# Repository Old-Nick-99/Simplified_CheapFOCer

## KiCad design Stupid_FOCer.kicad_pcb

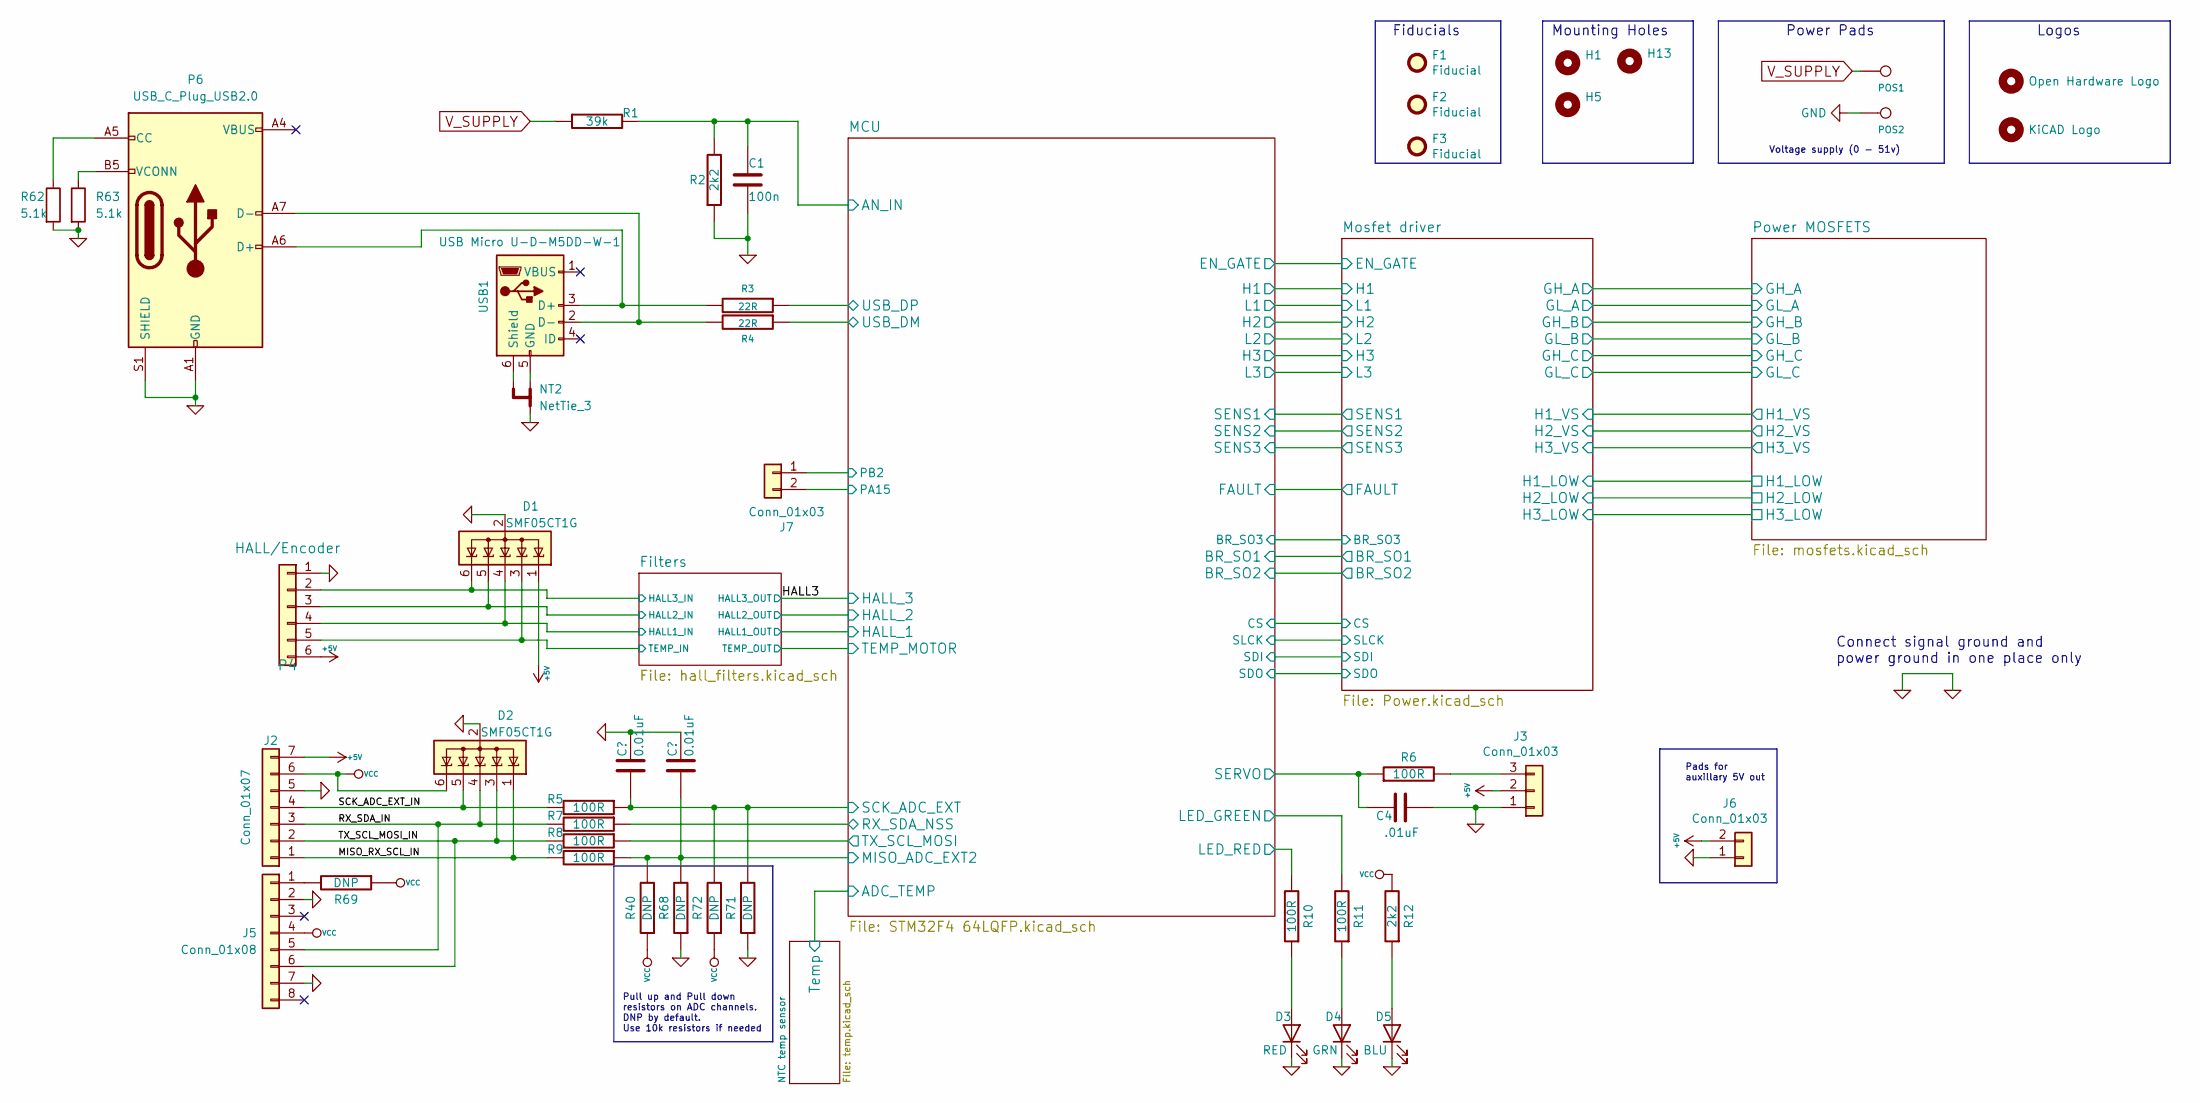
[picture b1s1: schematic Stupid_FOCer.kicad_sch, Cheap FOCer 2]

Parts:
C1: 100n; C_0603_1608Metric
C2, C3: 0.01uF; C_0603_1608Metric
C4: .01uF; C_0603_1608Metric
D1, D2: SMF05CT1G; SOT-363_SC-70-6
D3: RED; LED_0603_1608Metric
D4: GRN; LED_0603_1608Metric
D5: BLU; LED_0603_1608Metric
F1, F2, F3: Fiducial; Fiducial_1mm_Dia_2mm_Outer
H1, H5, H13: MountingHole; MountingHole_3.2mm_M3_ISO14580
H4: Open Hardware Logo; OSHW-Logo2_9.8x8mm_SilkScreen
H9: KiCAD Logo; KiCad-Logo2_5mm_SilkScreen
J2: Conn_01x07; JST_PH_B7B-PH-K_1x07_P2.00mm_Vertical
J3: Conn_01x03; JST_PH_B3B-PH-K_1x03_P2.00mm_Vertical
J5: Conn_01x08; PinSocket_1x08_P2.54mm_Vertical
J6, J7: Conn_01x03; PinHeader_1x02_P2.54mm_Vertical
NT2: NetTie_3; NetTie-3_SMD_Pad0.5mm
P4: HALL/Encoder; JST_PH_B6B-PH-K_1x06_P2.00mm_Vertical
P6: USB_C_Plug_USB2.0; USB_C_Receptacle_JAE_DX07S016JA1R1500
POS1, POS2: POS; MountingPad
R1: 39k; R_0603_1608Metric
R2, R12: 2k2; R_0603_1608Metric
R3, R4: 22R; R_0603_1608Metric
R5, R6, R7, R8, R9, R10, R11: 100R; R_0603_1608Metric
R40, R68, R69, R71, R72: DNP; R_0603_1608Metric
R62, R63: 5.1k; R_0603_1608Metric
USB1: USB Micro U-D-M5DD-W-1; USB_Micro-B_Wuerth_614105150721_Vertical

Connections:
+5V: D1.1 (K), J2.7, J3.2, J6.2, P4.6; also elsewhere on the board
/Filters/HALL1_IN: D1.4 (K), P4.4; also elsewhere on the board
/Filters/HALL2_IN: D1.5 (K), P4.3; also elsewhere on the board
/Filters/TEMP_IN: D1.3 (K), P4.5; also elsewhere on the board
/HALL3: D1.6 (K), P4.2; also elsewhere on the board
/MCU/AN_IN: C1.2, R1.2, R2.2; also elsewhere on the board
/MCU/LED_GREEN: R11.2; also elsewhere on the board
/MCU/LED_RED: R10.2; also elsewhere on the board
/MCU/MISO_ADC_EXT2: C3.2, R9.1, R40.2, R68.2; also elsewhere on the board
/MCU/RX_SDA_NSS: R7.1; also elsewhere on the board
/MCU/SCK_ADC_EXT: C2.2, R5.1, R71.2, R72.2; also elsewhere on the board
/MCU/SERVO: C4.2, R6.1; also elsewhere on the board
/MCU/TX_SCL_MOSI: R8.1; also elsewhere on the board
/MCU/USB_DM: R4.1; also elsewhere on the board
/MCU/USB_DP: R3.1; also elsewhere on the board
/MISO_RX_SCL_IN: D2.1 (K), J2.1, R9.2
/RX_SDA_IN: D2.4 (K), J2.3, J5.5, R7.2
/SCK_ADC_EXT_IN: D2.5 (K), J2.4, R5.2
/TX_SCL_MOSI_IN: D2.3 (K), J2.2, J5.6, R8.2
unnamed: D3.2 (A), R10.1
unnamed: D4.2 (A), R11.1
unnamed: D5.2 (A), R12.1
unnamed: J3.3, R6.2
unnamed: J5.1, R69.2
unnamed: P6.A5 (CC), R62.1
unnamed: P6.A6 (D+), R3.2, USB1.3 (D+)
unnamed: P6.A7 (D-), R4.2, USB1.2 (D-)
unnamed: P6.B5 (VCONN), R63.1
unnamed: NT2.1, USB1.5 (GND)
unnamed: NT2.3, USB1.6 (Shield)
PA15: J7.2; also elsewhere on the board
PB2: J7.1; also elsewhere on the board
VCC: D2.6 (K), J2.6, J5.4, R12.2, R40.1, R69.1, R72.1; also elsewhere on the board
V_SUPPLY: POS1.1, R1.1; also elsewhere on the board

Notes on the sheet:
Power Pads
Fiducials
Logos
Mounting Holes
Connect signal ground and power ground in one place only
Voltage supply (0 - 51v)
Pads for auxillary 5V out
Pull up and Pull down resistors on ADC channels. DNP by default. Use 10k resistors if needed

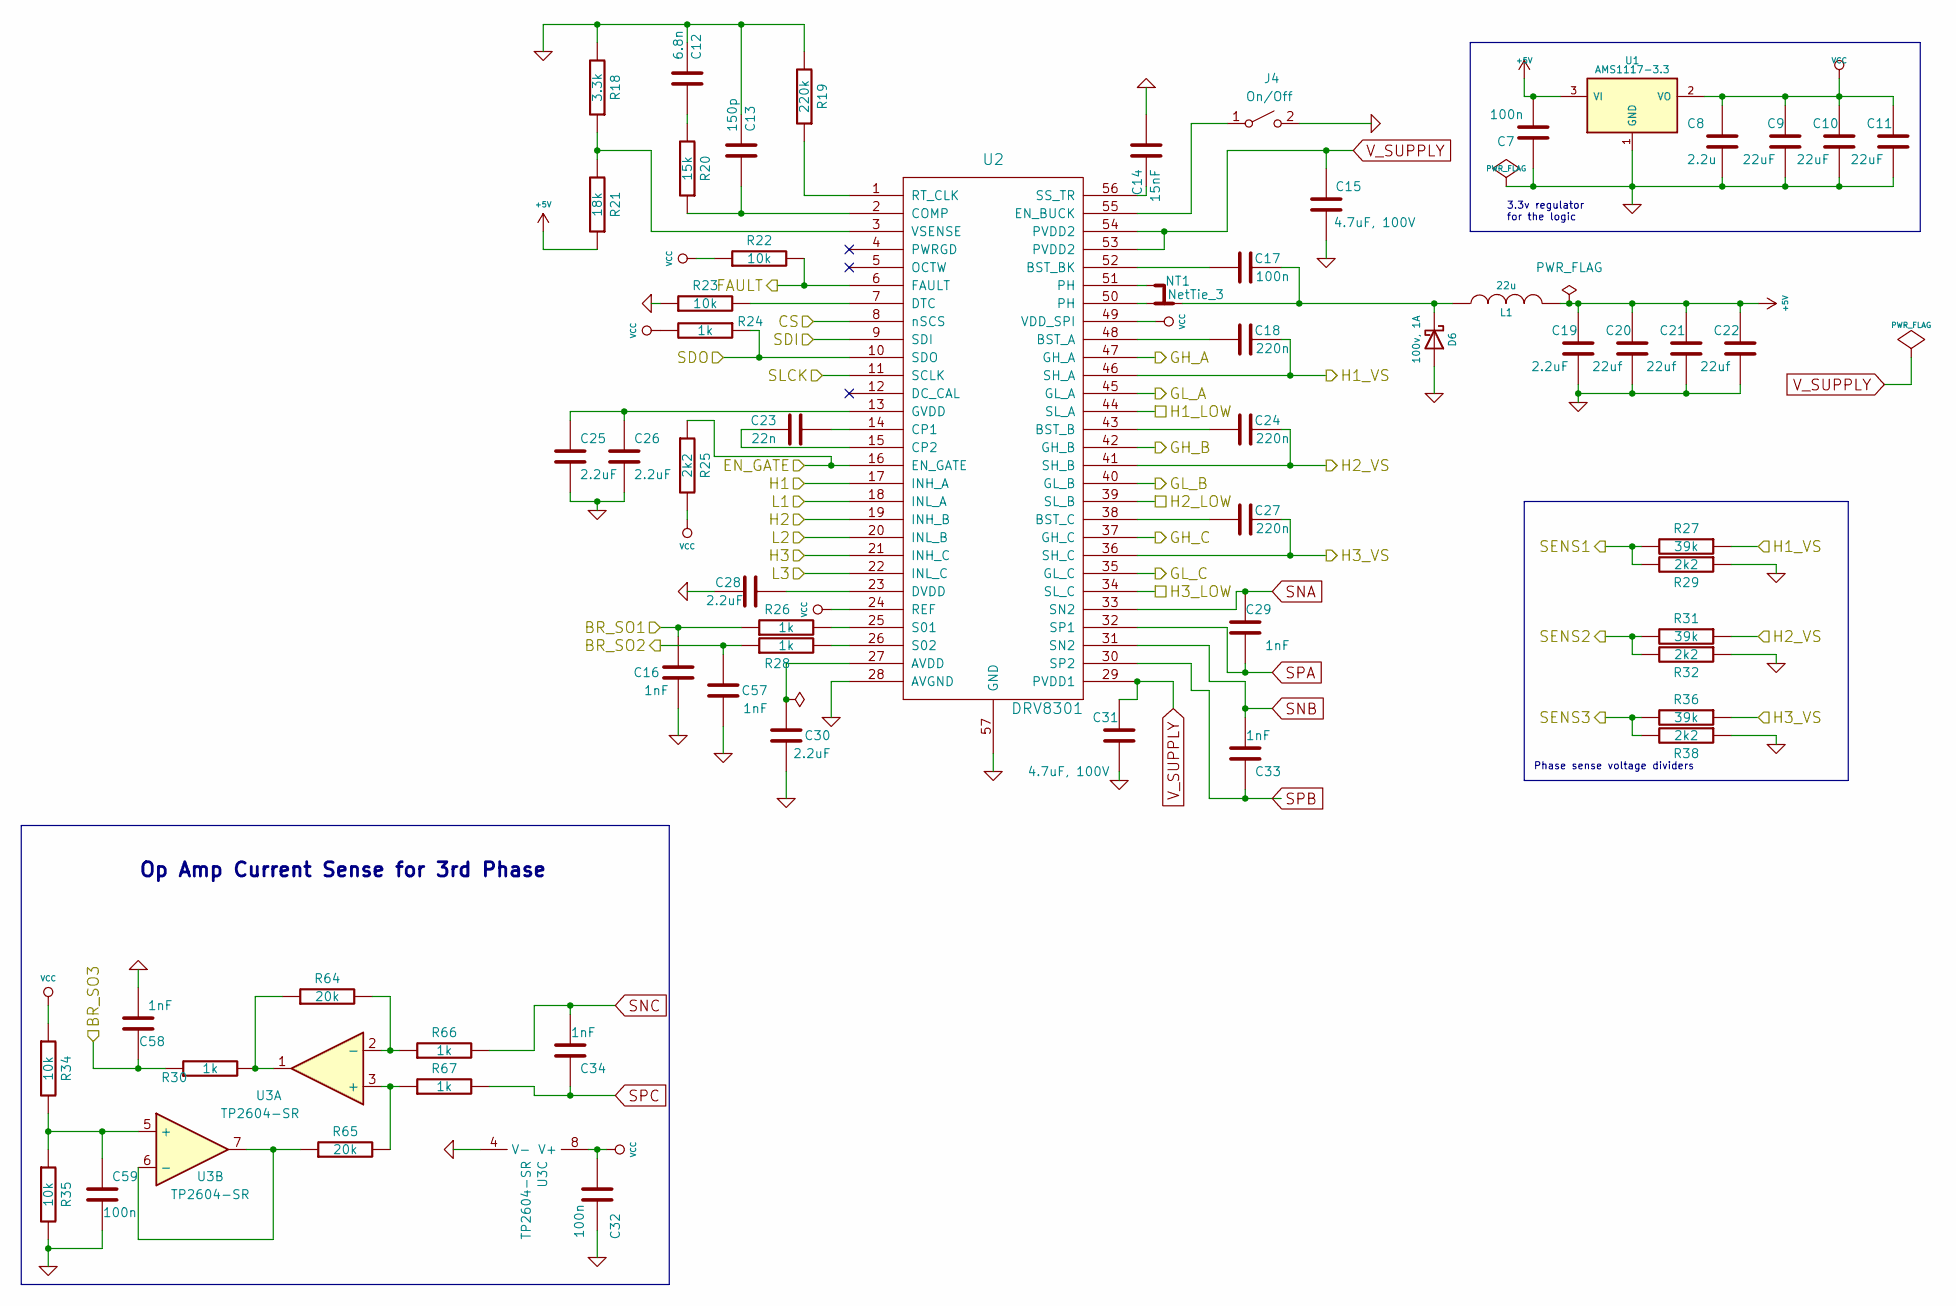
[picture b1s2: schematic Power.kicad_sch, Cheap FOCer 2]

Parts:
C7, C17, C32, C59: 100n; C_0603_1608Metric
C8: 2.2u; C_0603_1608Metric
C9, C10, C11: 22uF; C_0805_2012Metric
C12: 6.8n; C_0603_1608Metric
C13: 150p; C_0603_1608Metric
C14: 15nF; C_0603_1608Metric
C15, C31: 4.7uF, 100V; C_1210_3225Metric
C16, C29, C33, C34, C57, C58: 1nF; C_0603_1608Metric
C18, C24, C27: 220n; C_0603_1608Metric
C19, C25, C26, C28, C30: 2.2uF; C_0603_1608Metric
C20, C21, C22: 22uf; C_0805_2012Metric
C23: 22n; C_0603_1608Metric
D6: 100v, 1A; D_SMA
J4: On/Off; JST_PH_B2B-PH-K_1x02_P2.00mm_Vertical
L1: 22u; L_Taiyo-Yuden_NR-60xx_HandSoldering
NT1: NetTie_3; NT3_Small
R18: 3.3k; R_0603_1608Metric
R19: 220k; R_0603_1608Metric
R20: 15k; R_0603_1608Metric
R21: 18k; R_0603_1608Metric
R22, R23, R34, R35: 10k; R_0603_1608Metric
R24, R26, R28, R30, R66, R67: 1k; R_0603_1608Metric
R25, R29, R32, R38: 2k2; R_0603_1608Metric
R27, R31, R36: 39k; R_0603_1608Metric
R64, R65: 20k; R_0603_1608Metric
U1: AMS1117-3.3; SOT-223-3_TabPin2
U2: DRV8301; HTSSOP-56-1EP_6.1x14mm_P0.5mm_EP3.61x6.35mm
U3: TP2604-SR; SOIC-8_3.9x4.9mm_P1.27mm

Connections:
+5V: C7.2, C19.2, C20.2, C21.2, C22.2, L1.2, R21.1, U1.3 (VI); also elsewhere on the board
/MCU/BR_SO1: C16.2, R26.1; also elsewhere on the board
/MCU/BR_SO2: C57.2, R28.1; also elsewhere on the board
/MCU/BR_SO3: C58.2, R30.1; also elsewhere on the board
/MCU/CS: U2.8 (nSCS); also elsewhere on the board
/MCU/EN_GATE: R25.1, U2.16 (EN_GATE); also elsewhere on the board
/MCU/FAULT: R22.2, U2.6 (FAULT); also elsewhere on the board
/MCU/H1: U2.17 (INH_A); also elsewhere on the board
/MCU/H2: U2.19 (INH_B); also elsewhere on the board
/MCU/H3: U2.21 (INH_C); also elsewhere on the board
/MCU/L1: U2.18 (INL_A); also elsewhere on the board
/MCU/L2: U2.20 (INL_B); also elsewhere on the board
/MCU/L3: U2.22 (INL_C); also elsewhere on the board
/MCU/SDI: U2.9 (SDI); also elsewhere on the board
/MCU/SDO: R24.1, U2.10 (SDO); also elsewhere on the board
/MCU/SENS1: R27.2, R29.2; also elsewhere on the board
/MCU/SENS2: R31.2, R32.2; also elsewhere on the board
/MCU/SENS3: R36.2, R38.2; also elsewhere on the board
/MCU/SLCK: U2.11 (SCLK); also elsewhere on the board
/Mosfet driver/GH_A: U2.47 (GH_A); also elsewhere on the board
/Mosfet driver/GH_B: U2.42 (GH_B); also elsewhere on the board
/Mosfet driver/GH_C: U2.37 (GH_C); also elsewhere on the board
/Mosfet driver/GL_A: U2.45 (GL_A); also elsewhere on the board
/Mosfet driver/GL_B: U2.40 (GL_B); also elsewhere on the board
/Mosfet driver/GL_C: U2.35 (GL_C); also elsewhere on the board
/Mosfet driver/H1_LOW: U2.44 (SL_A); also elsewhere on the board
/Mosfet driver/H1_VS: C18.2, R27.1, U2.46 (SH_A); also elsewhere on the board
/Mosfet driver/H2_LOW: U2.39 (SL_B); also elsewhere on the board
/Mosfet driver/H2_VS: C24.2, R31.1, U2.41 (SH_B); also elsewhere on the board
/Mosfet driver/H3_LOW: U2.34 (SL_C); also elsewhere on the board
/Mosfet driver/H3_VS: C27.2, R36.1, U2.36 (SH_C); also elsewhere on the board
unnamed: C12.2, R20.2
unnamed: C17.2, D6.1 (K), L1.1, NT1.2
unnamed: J4.1 (A), U2.55 (EN_BUCK)
unnamed: NT1.1, U2.50 (PH)
unnamed: NT1.3, U2.51 (PH)
unnamed: R30.2, R64.1, U3.1
unnamed: C30.2, U2.27 (AVDD)
unnamed: C18.1, U2.48 (BST_A)
unnamed: C24.1, U2.43 (BST_B)
unnamed: C17.1, U2.52 (BST_BK)
unnamed: C27.1, U2.38 (BST_C)
unnamed: C13.2, R20.1, U2.2 (COMP)
unnamed: C23.2, U2.14 (CP1)
unnamed: C23.1, U2.15 (CP2)
unnamed: R23.2, U2.7 (DTC)
unnamed: C28.1, U2.23 (DVDD)
unnamed: C25.1, C26.1, U2.13 (GVDD)
unnamed: R19.1, U2.1 (RT_CLK)
unnamed: R26.2, U2.25 (S01)
unnamed: R28.2, U2.26 (S02)
unnamed: C14.1, U2.56 (SS_TR)
unnamed: R18.1, R21.2, U2.3 (VSENSE)
unnamed: R65.2, R67.1, U3.3 (+)
unnamed: R64.2, R66.1, U3.2 (-)
unnamed: C59.1, R34.2, R35.1, U3.5 (+)
unnamed: R65.1, U3.6 (-), U3.7
SNA: C29.2, U2.33 (SN2); also elsewhere on the board
SNB: C33.1, U2.31 (SN2); also elsewhere on the board
SNC: C34.1, R66.2; also elsewhere on the board
SPA: C29.1, U2.32 (SP1); also elsewhere on the board
SPB: C33.2, U2.30 (SP2); also elsewhere on the board
SPC: C34.2, R67.2; also elsewhere on the board
VCC: C8.1, C9.2, C10.2, C11.2, C32.2, R22.1, R24.2, R25.2, R34.1, U1.2 (VO), U2.24 (REF), U2.49 (VDD_SPI), U3.8 (V+); also elsewhere on the board
V_SUPPLY: C15.2, C31.2, U2.29 (PVDD1), U2.53 (PVDD2), U2.54 (PVDD2); also elsewhere on the board

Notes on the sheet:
Phase sense voltage dividers
3.3v regulator for the logic
Op Amp Current Sense for 3rd Phase

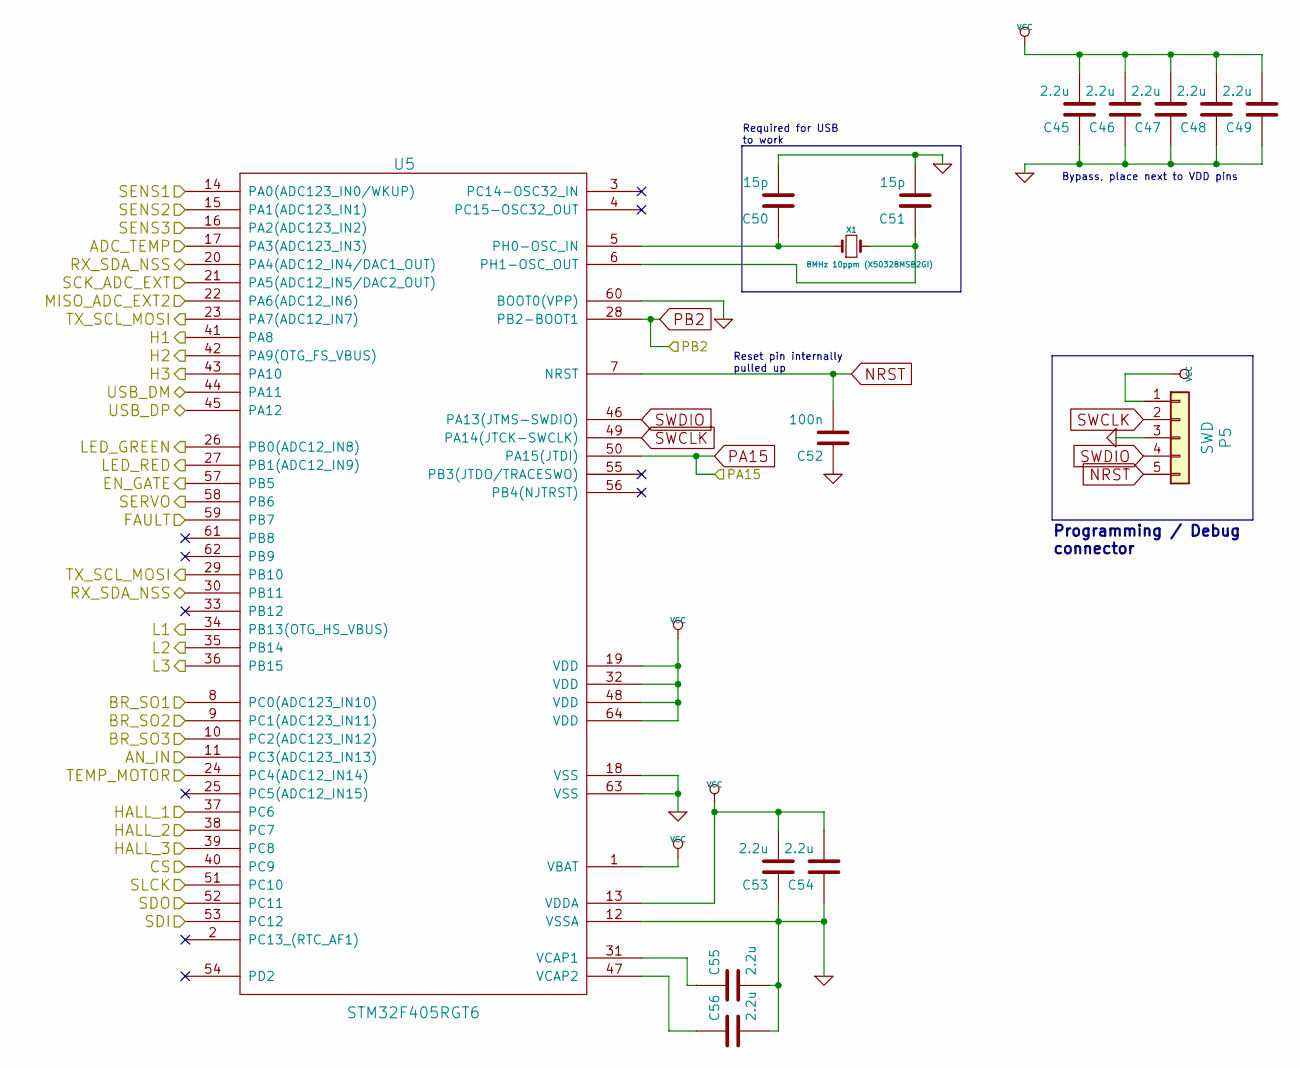
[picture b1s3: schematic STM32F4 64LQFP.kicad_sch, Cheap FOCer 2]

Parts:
C45, C46, C47, C48, C49, C53, C54, C55, C56: 2.2u; C_0603_1608Metric
C50, C51: 15p; C_0603_1608Metric
C52: 100n; C_0603_1608Metric
P5: SWD; PinHeader_1x05_P2.54mm_Vertical
U5: STM32F405RGT6; LQFP-64_10x10mm_P0.5mm
X1: 8MHz 10ppm (X50328MSB2GI); Crystal_SMD_5032-2Pin_5.0x3.2mm; mfg# ABM3B-8.0-10-1UT

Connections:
/Filters/HALL1_IN: U5.37 (PC6); also elsewhere on the board
/Filters/HALL2_IN: U5.38 (PC7); also elsewhere on the board
/Filters/TEMP_IN: U5.24 (PC4(ADC12_IN14)); also elsewhere on the board
/HALL3: U5.39 (PC8); also elsewhere on the board
/MCU/ADC_TEMP: U5.17 (PA3(ADC123_IN3)); also elsewhere on the board
/MCU/AN_IN: U5.11 (PC3(ADC123_IN13)); also elsewhere on the board
/MCU/BR_SO1: U5.8 (PC0(ADC123_IN10)); also elsewhere on the board
/MCU/BR_SO2: U5.9 (PC1(ADC123_IN11)); also elsewhere on the board
/MCU/BR_SO3: U5.10 (PC2(ADC123_IN12)); also elsewhere on the board
/MCU/CS: U5.40 (PC9); also elsewhere on the board
/MCU/EN_GATE: U5.57 (PB5); also elsewhere on the board
/MCU/FAULT: U5.59 (PB7); also elsewhere on the board
/MCU/H1: U5.41 (PA8); also elsewhere on the board
/MCU/H2: U5.42 (PA9(OTG_FS_VBUS)); also elsewhere on the board
/MCU/H3: U5.43 (PA10); also elsewhere on the board
/MCU/L1: U5.34 (PB13(OTG_HS_VBUS)); also elsewhere on the board
/MCU/L2: U5.35 (PB14); also elsewhere on the board
/MCU/L3: U5.36 (PB15); also elsewhere on the board
/MCU/LED_GREEN: U5.26 (PB0(ADC12_IN8)); also elsewhere on the board
/MCU/LED_RED: U5.27 (PB1(ADC12_IN9)); also elsewhere on the board
/MCU/MISO_ADC_EXT2: U5.22 (PA6(ADC12_IN6)); also elsewhere on the board
/MCU/RX_SDA_NSS: U5.20 (PA4(ADC12_IN4/DAC1_OUT)), U5.30 (PB11); also elsewhere on the board
/MCU/SCK_ADC_EXT: U5.21 (PA5(ADC12_IN5/DAC2_OUT)); also elsewhere on the board
/MCU/SDI: U5.53 (PC12); also elsewhere on the board
/MCU/SDO: U5.52 (PC11); also elsewhere on the board
/MCU/SENS1: U5.14 (PA0(ADC123_IN0/WKUP)); also elsewhere on the board
/MCU/SENS2: U5.15 (PA1(ADC123_IN1)); also elsewhere on the board
/MCU/SENS3: U5.16 (PA2(ADC123_IN2)); also elsewhere on the board
/MCU/SERVO: U5.58 (PB6); also elsewhere on the board
/MCU/SLCK: U5.51 (PC10); also elsewhere on the board
/MCU/TX_SCL_MOSI: U5.23 (PA7(ADC12_IN7)), U5.29 (PB10); also elsewhere on the board
/MCU/USB_DM: U5.44 (PA11); also elsewhere on the board
/MCU/USB_DP: U5.45 (PA12); also elsewhere on the board
NRST: C52.2, P5.5, U5.7 (NRST)
unnamed: C50.1, U5.5 (PH0-OSC_IN), X1.1
unnamed: C51.1, U5.6 (PH1-OSC_OUT), X1.2
unnamed: C55.1, U5.31 (VCAP1)
unnamed: C56.1, U5.47 (VCAP2)
PA15: U5.50 (PA15(JTDI)); also elsewhere on the board
PB2: U5.28 (PB2-BOOT1); also elsewhere on the board
SWCLK: P5.2, U5.49 (PA14(JTCK-SWCLK))
SWDIO: P5.4, U5.46 (PA13(JTMS-SWDIO))
VCC: C45.2, C46.2, C47.2, C48.2, C49.2, C53.2, C54.2, P5.1, U5.1 (VBAT), U5.13 (VDDA), U5.19 (VDD), U5.32 (VDD), U5.48 (VDD), U5.64 (VDD); also elsewhere on the board

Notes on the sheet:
Required for USB to work
Programming / Debug connector
Bypass, place next to VDD pins
Reset pin internally pulled up

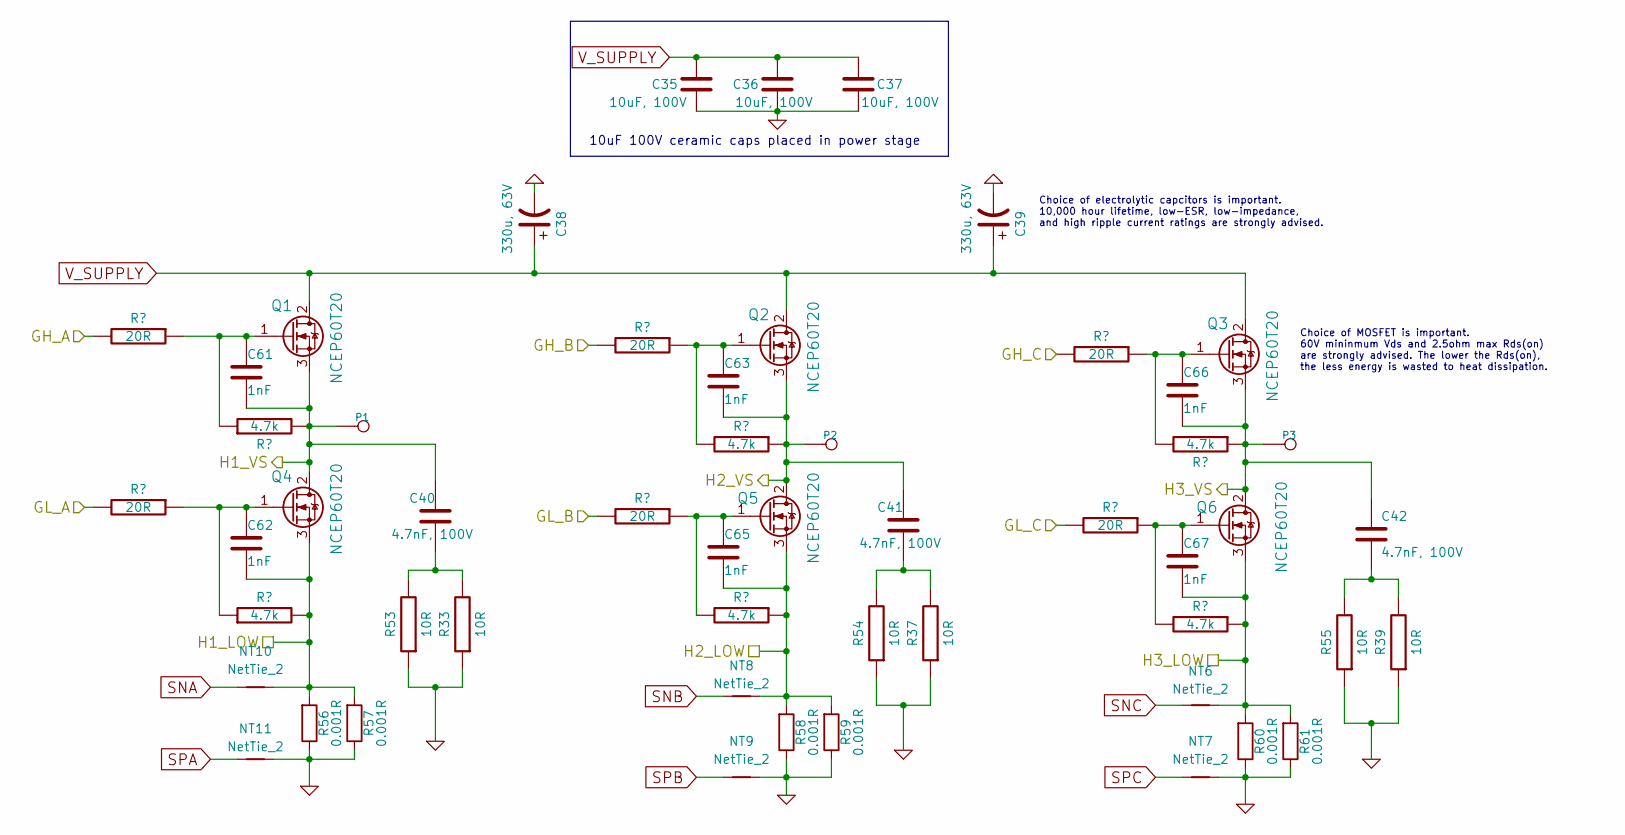
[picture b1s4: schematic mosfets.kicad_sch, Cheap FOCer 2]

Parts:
C35, C36, C37: 10uF, 100V; C_2220_5650Metric_Pad1.97x5.40mm_HandSolder
C38, C39: 330u, 63V; CP_10x20mm_hor_with_model_brd_edge
C40, C41, C42: 4.7nF, 100V; C_0805_2012Metric
C61, C62, C63, C65, C66, C67: 1nF; C_0603_1608Metric
NT6, NT7, NT8, NT9, NT10, NT11: NetTie_2; NetTie-2_SMD_Pad0.5mm
P1, P2, P3: MOTOR1; MountingPad
Q1, Q2, Q3, Q4, Q5, Q6: NCEP60T20; TO-220-3_Horizontal_TabUp_no_hole
R33, R37, R39, R53, R54, R55: 10R; R_0805_2012Metric
R41, R42, R43, R47, R48, R49: 20R; R_0805_2012Metric
R44, R45, R46, R50, R51, R52: 4.7k; R_0603_1608Metric
R56, R57, R58, R59, R60, R61: 0.001R; R_2512_Yageo_big_pads

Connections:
/Mosfet driver/GH_A: R41.2; also elsewhere on the board
/Mosfet driver/GH_B: R42.2; also elsewhere on the board
/Mosfet driver/GH_C: R43.2; also elsewhere on the board
/Mosfet driver/GL_A: R47.2; also elsewhere on the board
/Mosfet driver/GL_B: R48.2; also elsewhere on the board
/Mosfet driver/GL_C: R49.2; also elsewhere on the board
/Mosfet driver/H1_LOW: C62.2, NT10.2, Q4.3 (S), R50.2, R56.2, R57.2; also elsewhere on the board
/Mosfet driver/H1_VS: C40.1, C61.2, P1.1, Q1.3 (S), Q4.2 (D), R44.2; also elsewhere on the board
/Mosfet driver/H2_LOW: C65.2, NT8.2, Q5.3 (S), R51.1, R58.2, R59.2; also elsewhere on the board
/Mosfet driver/H2_VS: C41.1, C63.2, P2.1, Q2.3 (S), Q5.2 (D), R45.1; also elsewhere on the board
/Mosfet driver/H3_LOW: C67.2, NT6.2, Q6.3 (S), R52.1, R60.2, R61.2; also elsewhere on the board
/Mosfet driver/H3_VS: C42.1, C66.2, P3.1, Q3.3 (S), Q6.2 (D), R46.1; also elsewhere on the board
unnamed: C40.2, R33.2, R53.2
unnamed: C41.2, R37.2, R54.2
unnamed: C42.2, R39.2, R55.2
unnamed: C61.1, Q1.1 (G), R41.1, R44.1
unnamed: C63.1, Q2.1 (G), R42.1, R45.2
unnamed: C66.1, Q3.1 (G), R43.1, R46.2
unnamed: C62.1, Q4.1 (G), R47.1, R50.1
unnamed: C65.1, Q5.1 (G), R48.1, R51.2
unnamed: C67.1, Q6.1 (G), R49.1, R52.2
SNA: NT10.1; also elsewhere on the board
SNB: NT8.1; also elsewhere on the board
SNC: NT6.1; also elsewhere on the board
SPA: NT11.1; also elsewhere on the board
SPB: NT9.1; also elsewhere on the board
SPC: NT7.1; also elsewhere on the board
V_SUPPLY: C35.2, C36.2, C37.2, C38.1, C39.1, Q1.2 (D), Q2.2 (D), Q3.2 (D); also elsewhere on the board

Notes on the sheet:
Choice of electrolytic capcitors is important. 10,000 hour lifetime, low-ESR, low-impedance, and high ripple current ratings are strongly advised.
Choice of MOSFET is important. 60V mininmum Vds and 2.5ohm max Rds(on) are strongly advised. The lower the Rds(on), the less energy is wasted to heat dissipation.
10uF 100V ceramic caps placed in power stage

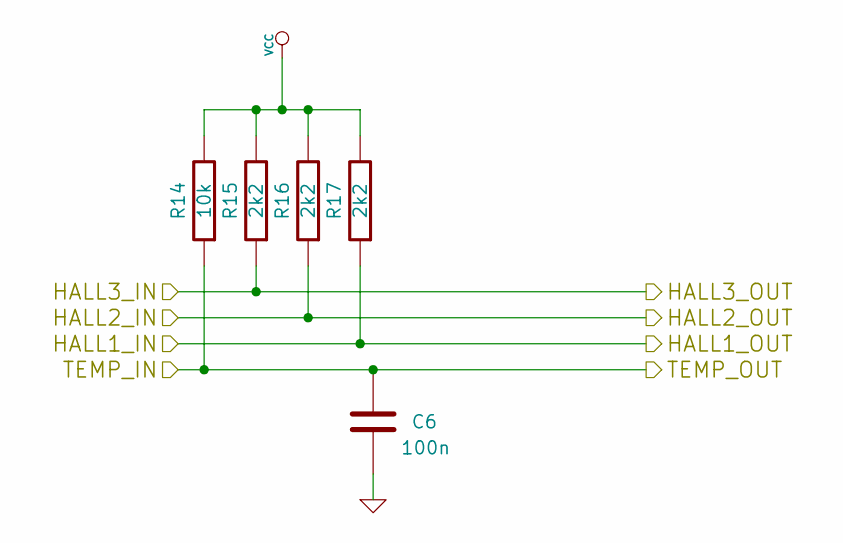
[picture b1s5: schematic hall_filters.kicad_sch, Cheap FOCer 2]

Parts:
C6: 100n; C_0603_1608Metric
R14: 10k; R_0603_1608Metric
R15, R16, R17: 2k2; R_0603_1608Metric

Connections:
/Filters/HALL1_IN: R17.1; also elsewhere on the board
/Filters/HALL2_IN: R16.1; also elsewhere on the board
/Filters/TEMP_IN: C6.2, R14.1; also elsewhere on the board
/HALL3: R15.1; also elsewhere on the board
VCC: R14.2, R15.2, R16.2, R17.2; also elsewhere on the board

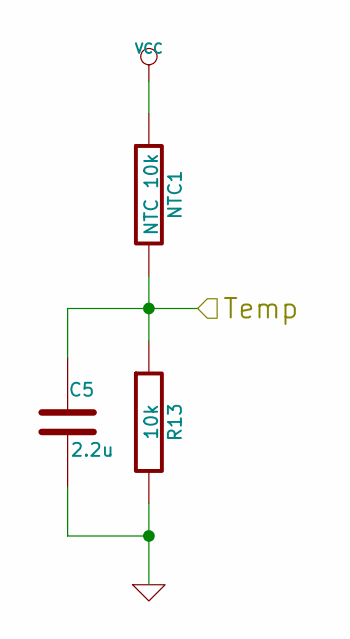
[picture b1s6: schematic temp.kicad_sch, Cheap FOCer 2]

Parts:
C5: 2.2u; C_0603_1608Metric
NTC1: NTC 10k; R_0603_1608Metric
R13: 10k; R_0603_1608Metric

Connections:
/MCU/ADC_TEMP: C5.1, NTC1.2, R13.1; also elsewhere on the board
VCC: NTC1.1; also elsewhere on the board

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
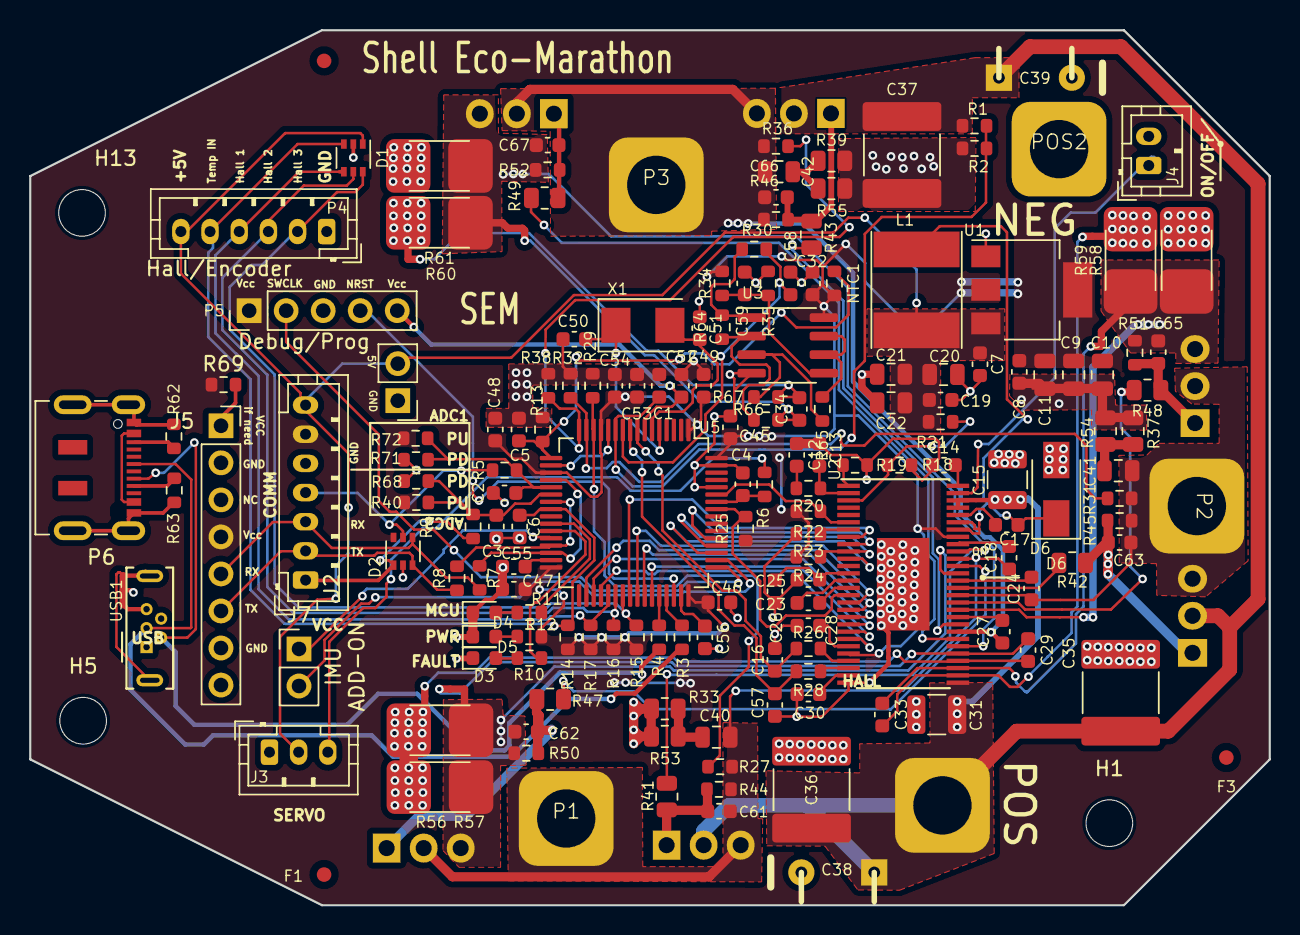
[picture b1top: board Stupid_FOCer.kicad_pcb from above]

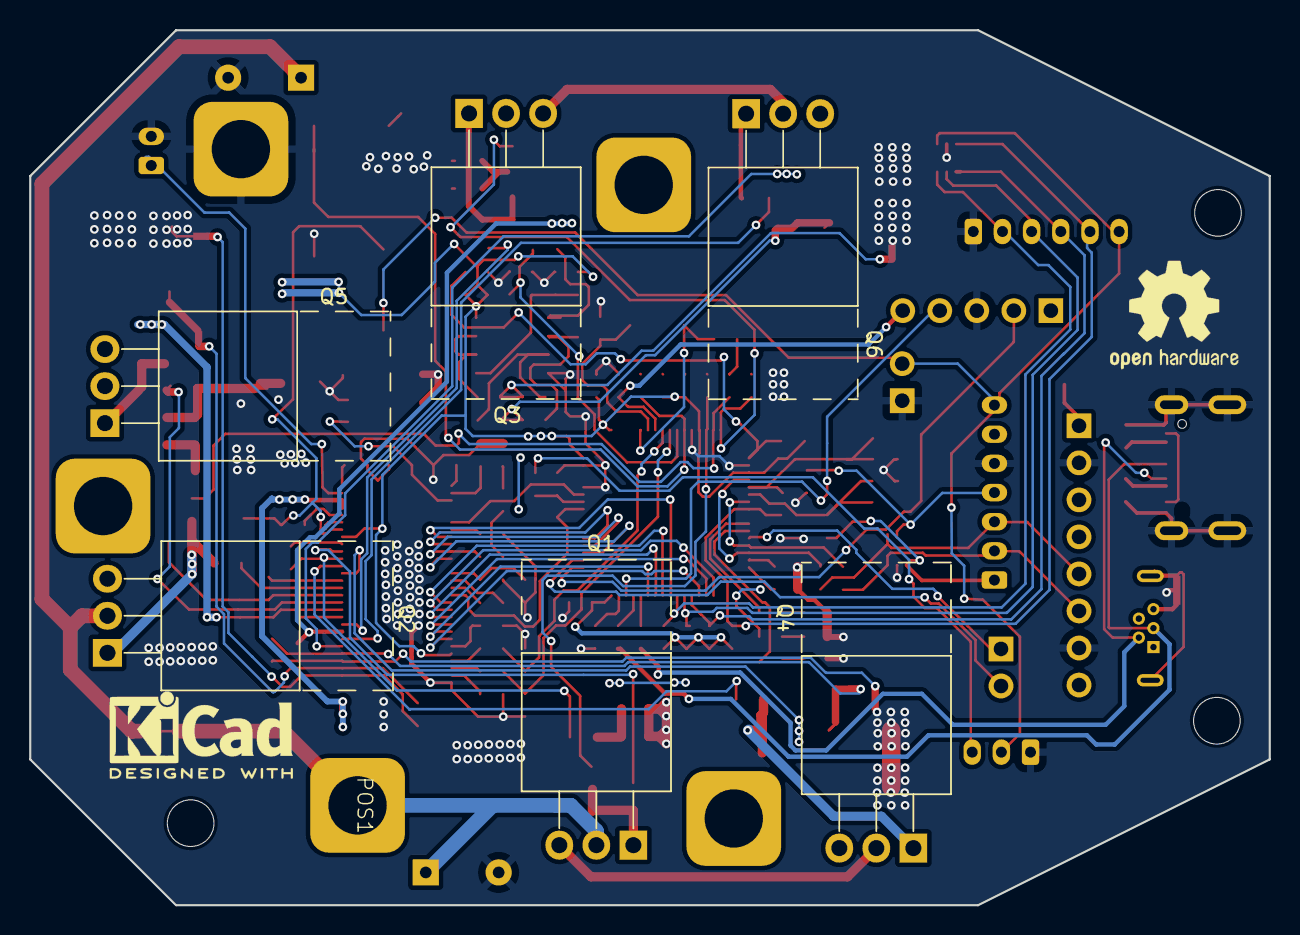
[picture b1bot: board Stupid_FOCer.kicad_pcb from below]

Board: 2 copper layers, 85.0 x 60.0 mm, 184 parts (9 on the bottom side), 114 nets.

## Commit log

2024-01-25 Added Gerber Files
2024-01-25 added supplementary documentation
